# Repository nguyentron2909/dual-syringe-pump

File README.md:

# Dual Syringe Pump Controller (ESP32 + TMC2209)

This repository contains the KiCad hardware design for a compact, battery-powered dual stepper motor controller. Designed around the **ESP32-WROOM-32** for wireless control and **TMC2209** silent stepper drivers, this board is optimized for high-precision multi-channel micropump systems and drug delivery applications.

## 🛠 Hardware Architecture

The project is divided into three main functional blocks:

### 1. Power Management & Charging
A robust power subsystem designed to handle both wall power and battery operation, ensuring uninterrupted dispensing.
* **Charging:** Integrated **TP5100** battery charger for 2S Li-ion setups.
* **Regulation:** * **Buck Converter (LM2596):** Stepping down input voltage to 5V for logic.
    * **LDO (AMS1117-3.3):** Providing stable 3.3V for the ESP32 and sensors.
    * **Dual Boost Converters (XL6009):** Independent 12V rails (`+12V_1` and `+12V_2`) to power the stepper drivers, allowing for high-torque performance even on battery power.

### 2. Main Control & Interface
The logic center of the board, featuring:
* **MCU:** ESP32-WROOM-32 with USB-C programming via **CH340C** and an auto-reset circuit.
* **Position Feedback:** Support for dual **AS5600** magnetic encoders via I2C for closed-loop monitoring and exact position tracking.
* **User Interface:** Headers for an external screen, status LEDs, and additional tactile buttons.

### 3. Stepper Driver Stage
High-performance motor control featuring:
* **Drivers:** Dual **TMC2209-LA** drivers (U6 & U7).
* **Communication:** UART interface mapped to the ESP32 for advanced configuration (StealthChop, StallGuard, dynamic current limits).
* **Optimization:** Support for hardware-level current sensing. *(Note: RS resistors should be desoldered from the current sensing module for better performance, as noted in the schematic).*

---

## 📋 Key Specifications

| Component | Specification |
| :--- | :--- |
| **Microcontroller** | ESP32-WROOM-32 (Wi-Fi/BT) |
| **Stepper Drivers** | 2x TMC2209 (SilentStepStick style) |
| **Input Voltage** | +12V Adapter or 2S Li-ion Battery |
| **Logic Voltage** | 3.3V and 5V |
| **Sensors** | 2x AS5600 Magnetic Encoders |
| **USB Interface** | USB-C (CH340C) |

---

## 📂 PCB layout

---

## 📝 Design Notes

* **Current Sensing:** Ensure you desolder the RS resistors from the driver modules if you are using an external current sensing setup to avoid interference.
* **Thermal Management:** Provide adequate cooling (heatsinks/airflow) for the XL6009 boost converters and TMC2209 drivers if running the stepper motors at high continuous currents.
* **Big thanks to google gemini for writting this for me :D

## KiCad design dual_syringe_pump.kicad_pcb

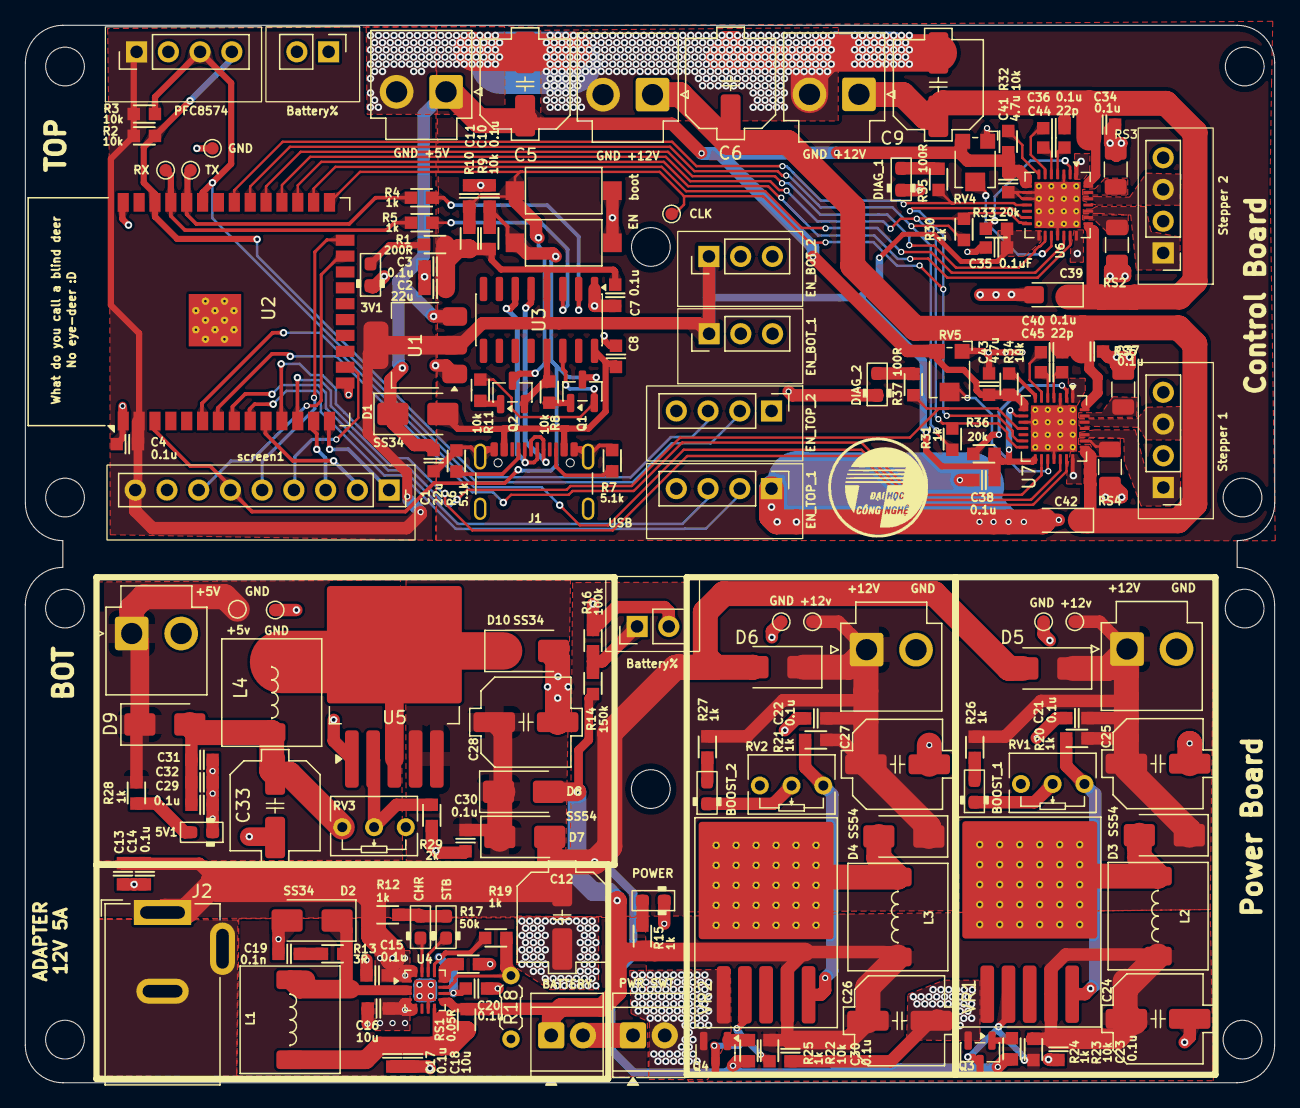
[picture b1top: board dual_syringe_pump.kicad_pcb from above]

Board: 2 copper layers, 100.0 x 84.6 mm, 161 parts (0 on the bottom side), 97 nets.

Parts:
3V1, 5V1: LED; LED_0603_1608Metric_Pad1.05x0.95mm
+5V    GND: buck; JST_VH_B2P-VH-B_1x02_P3.96mm_Vertical
+12V     GND: boost_2; JST_VH_B2P-VH-B_1x02_P3.96mm_Vertical
+12V     GND#2: boost_1; JST_VH_B2P-VH-B_1x02_P3.96mm_Vertical
BATTERY: Bat_protected; TerminalBlock_TE_282834-2_1x02_P2.54mm_Horizontal
BOOST_1, BOOST_2: LED; LED_0603_1608Metric_Pad1.05x0.95mm
Battery%: battery _percentage; PinHeader_1x02_P2.54mm_Vertical
Battery%#2: battery _percentage; PinHeader_1x02_P2.54mm_Vertical
C1, C2: 22u; C_0603
C3, C4, C7, C10, C13, C15, C17, C20, C21, C22, C23, C30, C30#2, C31, C34, C36, C37, C38, C40: 0.1u; C_0603
C5, C6, C9, C12, C25, C27, C28, C33: 100uF; C_Elec_6.3x7.7
C8, C11, C14, C29, C32, C35: 0.1uF; C_0603
C16, C18: 10u; C_0603
C19: 0.1n; C_0603
C24, C26: 330uF; C_Elec_6.3x7.7
C39, C42: 100uF; CP_EIA-3216-12_Kemet-S_HandSolder
C41, C43: 4.7u; C_0603
C44, C45: 22p; C_0603
CHR: LED; LED_0603_1608Metric_Pad1.05x0.95mm
D1, D2, D9, D10: SS34; D_SMA
D3, D4, D5, D6, D7, D8: SS54; D_SMA
DIAG_1, DIAG_2: LED; LED_0603_1608Metric_Pad1.05x0.95mm
EN_BOT_1, EN_BOT_2: Conn_01x03; PinHeader_1x03_P2.54mm_Vertical
EN_TOP_1, EN_TOP_2: Conn_01x04; PinHeader_1x04_P2.54mm_Vertical
GND: TestPoint; TestPoint_Pad_D1.0mm
GND +5V: buck; JST_VH_B2P-VH-B_1x02_P3.96mm_Vertical
GND +12V: boost_2; JST_VH_B2P-VH-B_1x02_P3.96mm_Vertical
GND +12V#2: boost_1; JST_VH_B2P-VH-B_1x02_P3.96mm_Vertical
J1: USB_C_Receptacle_USB2.0_16P; USB_C_Receptacle_GCT_USB4105-xx-A_16P_TopMnt_Horizontal
J2: Barrel_Jack_Switch_Pin3Ring; BarrelJack_GCT_DCJ200-10-A_Horizontal
L1: 22uH; L_7.3x7.3_H4.5
L2, L3: 47uH; L_7.3x7.3_H4.5
L4: 33uH; L_7.3x7.3_H4.5
PFC8574: Conn_01x04; PinHeader_1x04_P2.54mm_Vertical
POWER: LED; LED_0603_1608Metric_Pad1.05x0.95mm
PWR SWT: pb; TerminalBlock_TE_282834-2_1x02_P2.54mm_Horizontal
Q1, Q2, Q3, Q4: SS8050; SOT-23
R1: 200R; R_0603
R2, R3, R8, R9, R10, R11, R22, R23, R32, R34: 10k; R_0603
R4, R5, R12, R15, R19, R20, R21, R24, R25, R26, R27, R28, R30, R31: 1k; R_0603
R6, R7: 5.1k; R_0603
R13: 3R; R_0603
R14: 150k; R_0603
R16: 100k; R_0603
R17: 50k; R_0603
R18: 47d 3950 (10K); R_Axial_DIN0204_L3.6mm_D1.6mm_P5.08mm_Horizontal
R29: 2k; R_0603
R33, R36: 20k; R_0603
R35, R37: 100R; R_0603
RS1: 0.05R; R_0603
RS2, RS3, RS4, RS5: 0.1R; R_1206_3216Metric
RV1, RV2, RV3: 10k; Potentiometer_Bourns_3266Y_Vertical
RV4, RV5: 20k; Potentiometer_Bourns_TC33X_Vertical
STB: LED; LED_0603_1608Metric_Pad1.05x0.95mm
SW1: boot; SW_SPST_CK_RS282G05A3
SW2: reset; SW_SPST_CK_RS282G05A3
Stepper 1, Stepper 2: Conn_01x04; PinHeader_1x04_P2.54mm_Vertical
TP1: clock; TestPoint_Pad_D1.0mm
TP2: rx; TestPoint_Pad_D1.0mm
TP3: tx; TestPoint_Pad_D1.0mm
TP4, TP5, TP6, TP7, TP8, TP9: TestPoint; TestPoint_Pad_D1.0mm
U1: AMS1117-3.3; SOT-223-3_TabPin2
U2: ESP32-WROOM-32
U3: CH340C; SOIC-16_3.9x9.9mm_P1.27mm
U4: TP5100; LQFN-16-1EP_3x3mm_P0.5mm_EP1.7x1.7mm
U5: XL4015; TO-263-5_TabPin3
U6, U7: TMC2209-LA; VQFN-28-1EP_5x5mm_P0.5mm_EP3.7x3.7mm_ThermalVias
VR1, VR2: XL6019; TO-263-5_TabPin6_ThermalVias
screen1: Conn_01x09_Pin; PinSocket_1x09_P2.54mm_Vertical

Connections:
+3.3V: C2.1, C3.1, C4.1, C7.1, C35.2, C38.2, EN_BOT_1.1, EN_BOT_2.1, PFC8574.1, R1.2, R2.1, R3.1, R9.1, R10.1, R33.1, R36.1, U1.2 (VO), U2.2 (VDD), U3.4 (V3), U6.15 (VCC_IO), U7.9 (MS1/AD0), U7.15 (VCC_IO), screen1.9
+5V: +5V GND.1, C1.1, C5.1, C41.2, C43.2, D1.1 (K), D9.1 (K), GND +5V.1, R28.2, R32.1, R34.1, RV4.3, RV5.3, TP8.1, U1.3 (VI), U6.8 (5VOUT), U7.8 (5VOUT)
+12V_1: +12V GND#2.1, C9.1, C21.1, C25.1, C34.1, C36.1, C39.1, D3.1 (K), D5.1 (K), GND +12V#2.1, R20.2, R26.2, TP4.1, U6.22 (VS), U6.28 (VS)
+12V_2: +12V GND.1, C6.1, C22.1, C27.1, C37.1, C40.1, C42.1, D4.1 (K), D6.1 (K), GND +12V.1, R21.2, R27.2, TP5.1, U7.22 (VS), U7.28 (VS)
/BACKLIGHT: U2.10 (IO25), screen1.2
/CS: U2.23 (IO15), screen1.7
/D+: J1.A6 (D+), J1.B6 (D+), U3.5 (UD+)
/D-: J1.A7 (D-), J1.B7 (D-), U3.6 (UD-)
/DC: U2.24 (IO2), screen1.5
/DTR: Q2.2 (E), R8.1, U3.13 (~DTR)
/MISO: U2.14 (IO12), screen1.1
/MOSI: U2.16 (IO13), screen1.4
/Power Circuits/FB: R29.2, RV3.2, U5.2 (FB)
/Power Circuits/NTC: R18.2 (-), R19.2, U4.11 (TS)
/Power Circuits/Vreg: C20.1, R19.1, U4.10 (VREG), U4.13 (CS)
/RST: Q1.2 (E), R11.2, U3.14 (~RTS)
/RX: R5.2, TP2.1, U2.35 (TXD0/IO1)
/SCK: U2.13 (IO14), screen1.3
/SCL: EN_TOP_2.3, PFC8574.4, R2.2, U2.36 (IO22)
/SCL1: EN_TOP_1.3, U2.8 (IO32)
/SDA: EN_TOP_2.2, PFC8574.3, R3.2, U2.33 (IO21)
/SDA1: EN_TOP_1.2, U2.9 (IO33)
/TX: R4.2, TP3.1, U2.34 (RXD0/IO3)
/esp_EN: C10.1, Q1.3 (C), R9.2, SW1.1, U2.3 (EN), screen1.6
Adapter_+12V: C12.1, C13.1, C14.1, C15.1, C16.1, D5.2 (A), D6.2 (A), D7.2 (A), J2.1, R12.1, R24.2, R25.2, U4.1 (VIN), U4.4 (VIN), U4.5 (VIN), U4.16 (VIN)
DIAG_1: R35.2, U2.31 (IO19), U6.11 (DIAG)
DIAG_2: R37.2, U2.12 (IO27), U7.11 (DIAG)
DIR_1: U2.26 (IO4), U6.19 (DIR)
DIR_2: U2.6 (IO34), U7.19 (DIR)
EN_1: U2.27 (IO16), U6.20 (STDBY)
EN_2: U2.11 (IO26), U7.20 (STDBY)
Earth: BATTERY.2 (-), C12.2, C13.2, C14.2, C15.2, C16.2, C17.2, C18.2, C19.2, C20.2, D2.2 (A), J2.2, J2.3, PWR SWT.1, R17.1, R18.1 (+), U4.7 (GND), U4.17 (EXP)
GND: 5V1.1 (K), +5V GND.2, +12V GND.2, +12V GND#2.2, BOOST_1.1 (K), BOOST_2.1 (K), Battery%.2, C21.2, C22.2, C23.2, C24.2, C25.2, C26.2, C27.2, C28.2, C29.2, C30.2, C30#2.2, C31.2, C32.2, C33.2, D10.2 (A), POWER.1 (K), PWR SWT.2, Q3.2 (E), Q4.2 (E), R16.2, R29.1, RV1.2, RV2.2, TP6.1, TP7.1, TP9.1, U5.1 (GND), VR1.1 (GND), VR2.1 (GND)
GND1: 3V1.1 (K), C1.2, C2.2, C3.2, C4.2, C5.2, C6.2, C7.2, C8.2, C9.2, C10.2, C11.2, C34.2, C35.1, C37.2, C38.1, C39.2, C41.1, C42.2, C43.1, DIAG_1.1 (K), DIAG_2.1 (K), EN_BOT_1.3, EN_BOT_2.3, EN_TOP_1.1, EN_TOP_2.1, GND.1, GND +5V.2, GND +12V.2, GND +12V#2.2, J1.A1 (GND), J1.A12 (GND), J1.B1 (GND), J1.B12 (GND), J1.S1 (SHIELD), PFC8574.2, R6.1, R7.2, RS2.2, RS3.2, RS4.2, RS5.2, RV4.1, RV5.1, SW1.2, SW2.2, U1.1 (GND), U2.1 (GND), U2.15 (GND), U2.38 (GND), U2.39 (GND), U3.1 (GND), U6.3 (GND), U6.9 (MS1/AD0), U6.10 (MS2/AD1), U6.18 (GND), U6.29 (GND), U7.3 (GND), U7.10 (MS2/AD1), U7.18 (GND), U7.29 (GND), screen1.8
unnamed: 3V1.2 (A), R1.1
unnamed: 5V1.2 (A), R28.1
unnamed: BOOST_1.2 (A), R26.1
unnamed: BOOST_2.2 (A), R27.1
unnamed: C19.1, R13.1
unnamed: CHR.2 (A), R12.2, STB.2 (A)
unnamed: CHR.1 (K), U4.15 (~CHRG)
unnamed: D2.1 (K), L1.1, R13.2, U4.2 (LX), U4.3 (LX)
unnamed: D3.2 (A), L2.2, VR1.3 (SW), VR1.6 (SW)
unnamed: D4.2 (A), L3.2, VR2.3 (SW), VR2.6 (SW)
unnamed: C28.1, C30.1, D7.1 (K), D8.1 (K), U5.4 (VC), U5.5 (VIN)
unnamed: C29.1, C31.1, C32.1, C33.1, D9.2 (A), L4.2, RV3.1
unnamed: D10.1 (K), L4.1, U5.3 (SW)
unnamed: DIAG_1.2 (A), R35.1
unnamed: DIAG_2.2 (A), R37.1
unnamed: J1.A5 (CC1), R6.2
unnamed: J1.B5 (CC2), R7.1
unnamed: Q1.1 (B), R8.2
unnamed: Q2.1 (B), R11.1
unnamed: Q3.1 (B), R24.1
unnamed: Q3.3 (C), R23.2, VR1.2 (EN)
unnamed: Q4.1 (B), R25.1
unnamed: Q4.3 (C), R22.2, VR2.2 (EN)
unnamed: STB.1 (K), U4.14 (~STDBY)
unnamed: Stepper 2.1, U6.24 (OA1)
unnamed: Stepper 2.2, U6.21 (OA2)
unnamed: Stepper 2.3, U6.26 (OB1)
unnamed: Stepper 2.4, U6.1 (OB2)
unnamed: Stepper 1.1, U7.24 (OA1)
unnamed: Stepper 1.2, U7.21 (OA2)
unnamed: Stepper 1.3, U7.26 (OB1)
unnamed: Stepper 1.4, U7.1 (OB2)
unnamed: R5.1, U3.3 (RXD)
unnamed: R4.1, U3.2 (TXD)
unnamed: R17.2, U4.12 (RTRICK)
unnamed: C17.1, C18.1, L1.2, RS1.2, U4.8 (VS)
unnamed: RS2.1, U6.23 (BRA)
unnamed: RS3.1, U6.27 (BRB)
unnamed: C44.2, U6.5 (CPI)
unnamed: C44.1, U6.4 (CPO)
unnamed: R32.2, U6.7 (SPREAD)
unnamed: C36.2, U6.6 (VCP)
unnamed: RV4.2, U6.17 (VREF)
unnamed: R33.2, U6.2 (~EN)
unnamed: RS4.1, U7.23 (BRA)
unnamed: RS5.1, U7.27 (BRB)
unnamed: C45.2, U7.5 (CPI)
unnamed: C45.1, U7.4 (CPO)
unnamed: R34.2, U7.7 (SPREAD)
unnamed: C40.2, U7.6 (VCP)
unnamed: RV5.2, U7.17 (VREF)
unnamed: R36.2, U7.2 (~EN)
unnamed: R20.1, RV1.3, VR1.5 (FB)
unnamed: R21.1, RV2.3, VR2.5 (FB)
unnamed: POWER.2 (A), R15.1
unnamed: Battery%.1, R14.2, R16.1
RX_TMC: R30.2, R31.2, U2.28 (IO17), U6.14 (~PD/UART), U7.14 (~PD/UART)
STEP_1: U2.29 (IO5), U6.16 (STEP)
STEP_2: U2.7 (IO35), U7.16 (STEP)
TX_TMC: R30.1, R31.1, U2.30 (IO18)
USB_5V: C8.1, D1.2 (A), J1.A4 (VBUS), J1.A9 (VBUS), J1.B4 (VBUS), J1.B9 (VBUS), U3.16 (VCC)
Vbat: BATTERY.1 (+), C23.1, C24.1, C26.1, C30#2.1, D8.2 (A), L2.1, L3.1, R14.1, R15.2, R22.1, R23.1, RS1.1, U4.9 (BAT), VR1.4 (VIN), VR2.4 (VIN)
esp32_CLK: C11.1, Q2.3 (C), R10.2, SW2.1, TP1.1, U2.25 (IO0), U6.13 (CLK), U7.13 (CLK)

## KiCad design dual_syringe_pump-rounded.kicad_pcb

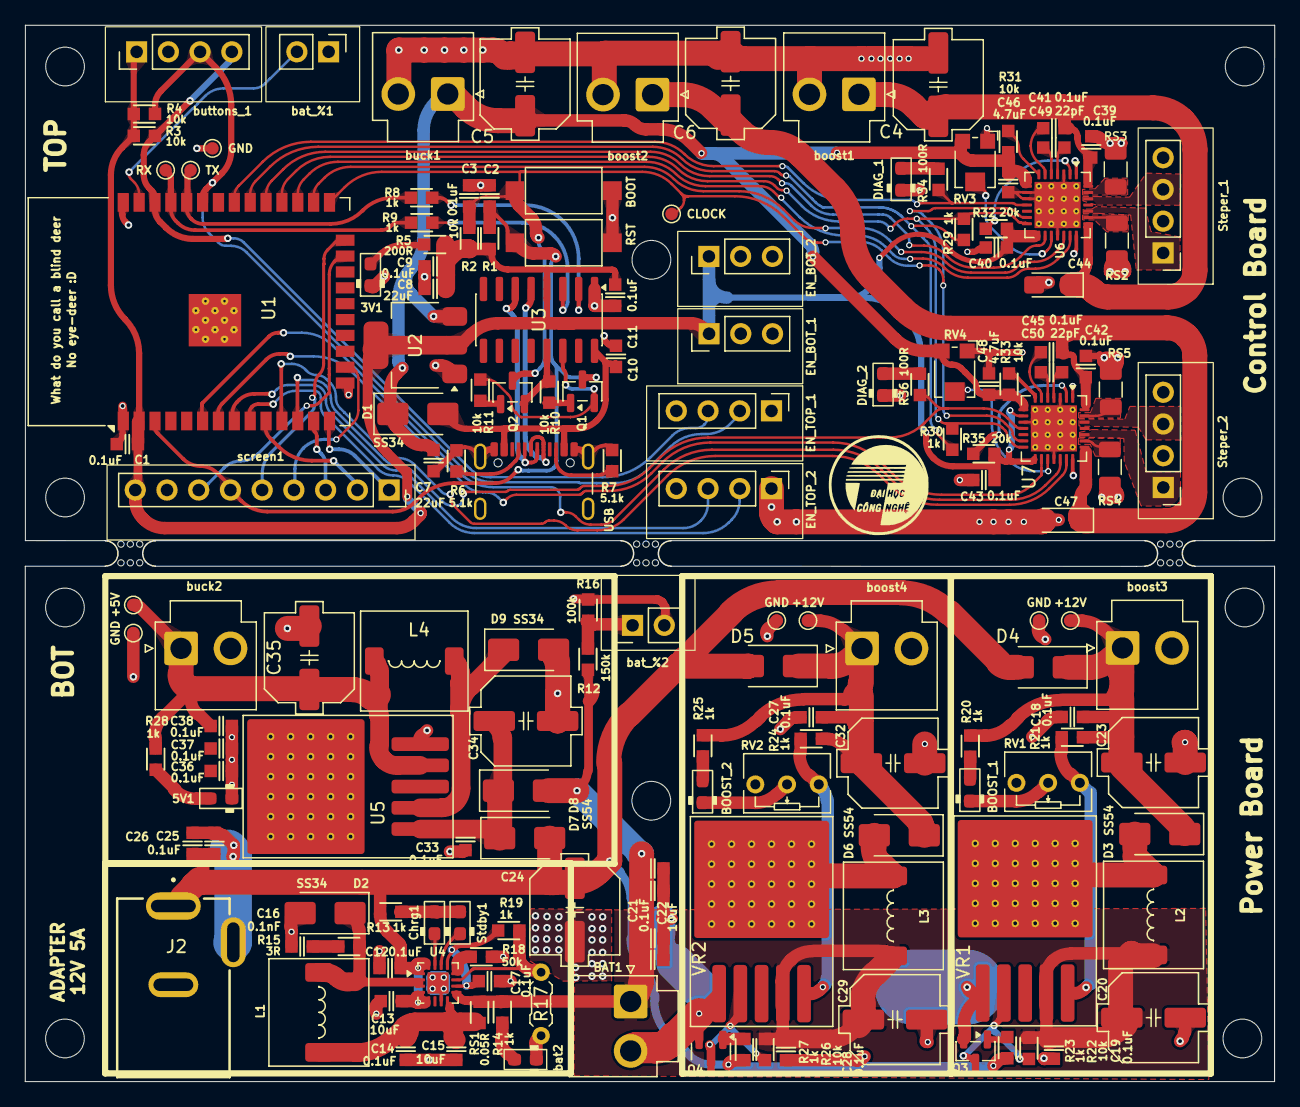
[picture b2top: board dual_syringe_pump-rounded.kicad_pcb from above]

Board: 2 copper layers, 100.0 x 84.6 mm, 164 parts (0 on the bottom side), 95 nets.

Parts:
3V1, 5V1: LED; LED_0603_1608Metric_Pad1.05x0.95mm
+5V, +12V, +12V#2: TestPoint; TestPoint_Pad_D1.0mm
BAT1: Bat_protected; JST_VH_B2P-VH-B_1x02_P3.96mm_Vertical
BOOST_1, BOOST_2: LED; LED_0603_1608Metric_Pad1.05x0.95mm
BOOT: reset; SW_SPST_CK_RS282G05A3
C1, C2, C3, C9, C10, C11, C12, C14, C17, C18, C19, C21, C25, C26, C27, C28, C30, C33, C36, C37, C38, C39, C40, C41, C42, C43, C45: 0.1uF; C_0603
C4, C5, C6, C23, C24, C32, C34, C35: 100uF; C_Elec_6.3x7.7
C7, C8: 22uF; C_0603
C13, C15, C22, C31: 10uF; C_0603
C16: 0.1nF; C_0603
C20, C29: 330uF; C_Elec_6.3x7.7
C44, C47: 100uF; CP_EIA-3216-12_Kemet-S_HandSolder
C46, C48: 4.7uF; C_0603
C49, C50: 22pF; C_0603
CLOCK: TestPoint; TestPoint_Pad_D1.0mm
Chrg1: LED; LED_0603_1608Metric_Pad1.05x0.95mm
D1, D2, D9: SS34; D_SMA
D3, D4, D5, D6, D7, D8: SS54; D_SMA
DIAG_1, DIAG_2: LED; LED_0603_1608Metric_Pad1.05x0.95mm
EN_BOT_1, EN_BOT_2: Conn_01x03; PinHeader_1x03_P2.54mm_Vertical
EN_TOP_1, EN_TOP_2: Conn_01x04; PinHeader_1x04_P2.54mm_Vertical
GND: TestPoint; TestPoint_Pad_D1.0mm
GND#2, GND#3, GND#4: TestPoint; TestPoint_Pad_D1.0mm
J2: Barrel_Jack_Switch_Pin3Ring; GCT_DCJ200-10-A-XX-K_REVA
L1: 22uH; L_7.3x7.3_H4.5
L2, L3: 47uH; L_7.3x7.3_H4.5
L4: 33uH; L_7.3x7.3_H4.5
Q1, Q2, Q3, Q4: SS8050; SOT-23
R1, R2, R3, R4, R10, R11, R22, R26, R31, R33: 10k; R_0603
R5: 200R; R_0603
R6, R7: 5.1k; R_0603
R8, R9, R13, R14, R19, R20, R21, R23, R24, R25, R27, R28, R29, R30: 1k; R_0603
R12: 150k; R_0603
R15: 3R; R_0603
R16: 100k; R_0603
R17: 47d 3950 (10K); R_Axial_DIN0204_L3.6mm_D1.6mm_P5.08mm_Horizontal
R18: 50k; R_0603
R32, R35: 20k; R_0603
R34, R36: 100R; R_0603
RS1: 0.05R; R_0603
RS2, RS3, RS4, RS5: 0.1R; R_1206_3216Metric
RST: boot; SW_SPST_CK_RS282G05A3
RV1, RV2: 10k; Potentiometer_Bourns_3266Y_Vertical
RV3, RV4: 20k; Potentiometer_Bourns_TC33X_Vertical
RX: TestPoint; TestPoint_Pad_D1.0mm
Stdby1: LED; LED_0603_1608Metric_Pad1.05x0.95mm
Steper_1, Steper_2: Conn_01x04; PinHeader_1x04_P2.54mm_Vertical
TX: TestPoint; TestPoint_Pad_D1.0mm
U1: ESP32-WROOM-32
U2: AMS1117-3.3; SOT-223-3_TabPin2
U3: CH340C; SOIC-16_3.9x9.9mm_P1.27mm
U4: TP5100; LQFN-16-1EP_3x3mm_P0.5mm_EP1.7x1.7mm
U5: LM2596S-buck; TO-263-5_TabPin3_ThermalVias
U6, U7: TMC2209-LA; VQFN-28-1EP_5x5mm_P0.5mm_EP3.7x3.7mm_ThermalVias
USB: USB_C_Receptacle_USB2.0_16P; USB_C_Receptacle_GCT_USB4105-xx-A_16P_TopMnt_Horizontal
VR1, VR2: XL6019; TO-263-5_TabPin6_ThermalVias
bat2: LED; LED_0603_1608Metric_Pad1.05x0.95mm
bat_%1, bat_%2: battery _percentage; PinHeader_1x02_P2.54mm_Vertical
boost1, boost3: boost_1; JST_VH_B2P-VH-B_1x02_P3.96mm_Vertical
boost2, boost4: boost_2; JST_VH_B2P-VH-B_1x02_P3.96mm_Vertical
buck1, buck2: buck; JST_VH_B2P-VH-B_1x02_P3.96mm_Vertical
buttons_1: Conn_01x04; PinHeader_1x04_P2.54mm_Vertical
mouse-bite-2mm-slot, mouse-bite-2mm-slot#2, mouse-bite-2mm-slot#3: VAL**; mouse-bite-2mm-slot
screen1: Conn_01x09_Pin; PinSocket_1x09_P2.54mm_Vertical

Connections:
+3.3V: C1.1, C8.1, C9.1, C11.1, C40.2, C43.2, EN_BOT_1.1, EN_BOT_2.1, R1.1, R2.1, R3.1, R4.1, R5.2, R32.1, R35.1, U1.2 (VDD), U2.2 (VO), U3.4 (V3), U6.15 (VCC_IO), U7.9 (MS1/AD0), U7.15 (VCC_IO), buttons_1.1, screen1.9
+5V: +5V.1, C5.1, C7.1, C35.1, C36.1, C37.1, C38.1, C46.2, C48.2, D1.1 (K), L4.2, R28.2, R31.1, R33.1, RV3.3, RV4.3, U2.3 (VI), U5.4 (FB), U6.8 (5VOUT), U7.8 (5VOUT), buck1.1, buck2.1
+12V_1: +12V#2.1, C4.1, C18.1, C23.1, C39.1, C41.1, C44.1, D3.1 (K), D4.1 (K), R20.2, R21.2, U6.22 (VS), U6.28 (VS), boost1.1, boost3.1
+12V_2: +12V.1, C6.1, C27.1, C32.1, C42.1, C45.1, C47.1, D5.1 (K), D6.1 (K), R24.2, R25.2, U7.22 (VS), U7.28 (VS), boost2.1, boost4.1
/BACKLIGHT: U1.10 (IO25), screen1.2
/BTN1: U1.37 (IO23), bat_%1.2
/CS: U1.23 (IO15), screen1.7
/D+: U3.5 (UD+), USB.A6 (D+), USB.B6 (D+)
/D-: U3.6 (UD-), USB.A7 (D-), USB.B7 (D-)
/DC: U1.24 (IO2), screen1.5
/DTR: Q2.2 (E), R10.1, U3.13 (~DTR)
/MISO: U1.14 (IO12), screen1.1
/MOSI: U1.16 (IO13), screen1.4
/Power Circuits/NTC: R17.2 (-), R19.2, U4.11 (TS)
/Power Circuits/Vreg: C17.1, R19.1, U4.10 (VREG), U4.13 (CS)
/RST: Q1.2 (E), R11.2, U3.14 (~RTS)
/RX: R9.2, RX.1, U1.35 (TXD0/IO1)
/SCK: U1.13 (IO14), screen1.3
/SCL: EN_TOP_1.3, R3.2, U1.36 (IO22), buttons_1.4
/SCL1: EN_TOP_2.3, U1.8 (IO32)
/SDA: EN_TOP_1.2, R4.2, U1.33 (IO21), buttons_1.3
/SDA1: EN_TOP_2.2, U1.9 (IO33)
/TX: R8.2, TX.1, U1.34 (RXD0/IO3)
/esp_EN: C2.1, Q1.3 (C), R1.2, RST.1, U1.3 (EN), screen1.6
Adapter_+12V: C12.1, C13.1, C24.1, C25.1, C26.1, D4.2 (A), D5.2 (A), D7.2 (A), J2.1, R13.1, R23.2, R27.2, U4.1 (VIN), U4.4 (VIN), U4.5 (VIN), U4.16 (VIN)
DIAG_1: R34.2, U1.31 (IO19), U6.11 (DIAG)
DIAG_2: R36.2, U1.12 (IO27), U7.11 (DIAG)
DIR_1: U1.26 (IO4), U6.19 (DIR)
DIR_2: U1.6 (IO34), U7.19 (DIR)
EN_1: U1.27 (IO16), U6.20 (STDBY)
EN_2: U1.11 (IO26), U7.20 (STDBY)
GND: 5V1.1 (K), BAT1.2 (-), BOOST_1.1 (K), BOOST_2.1 (K), C12.2, C13.2, C14.2, C15.2, C16.2, C17.2, C18.2, C19.2, C20.2, C21.2, C22.2, C23.2, C24.2, C25.2, C26.2, C27.2, C28.2, C29.2, C30.2, C31.2, C32.2, C33.2, C34.2, C35.2, C36.2, C37.2, C38.2, D2.2 (A), D9.2 (A), GND#2.1, GND#3.1, GND#4.1, J2.2, J2.3, Q3.2 (E), Q4.2 (E), R16.2, R17.1 (+), R18.1, RV1.2, RV2.2, U4.7 (GND), U4.17 (EXP), U5.3 (GND), U5.5 (~ON/OFF), VR1.1 (GND), VR2.1 (GND), bat2.1 (K), bat_%2.2, boost3.2, boost4.2, buck2.2
GND1: 3V1.1 (K), BOOT.2, C1.2, C2.2, C3.2, C4.2, C5.2, C6.2, C7.2, C8.2, C9.2, C10.2, C11.2, C39.2, C40.1, C42.2, C43.1, C44.2, C46.1, C47.2, C48.1, DIAG_1.1 (K), DIAG_2.1 (K), EN_BOT_1.3, EN_BOT_2.3, EN_TOP_1.1, EN_TOP_2.1, GND.1, R6.1, R7.2, RS2.2, RS3.2, RS4.2, RS5.2, RST.2, RV3.1, RV4.1, U1.1 (GND), U1.15 (GND), U1.38 (GND), U1.39 (GND), U2.1 (GND), U3.1 (GND), U6.3 (GND), U6.9 (MS1/AD0), U6.10 (MS2/AD1), U6.18 (GND), U6.29 (GND), U7.3 (GND), U7.10 (MS2/AD1), U7.18 (GND), U7.29 (GND), USB.A1 (GND), USB.A12 (GND), USB.B1 (GND), USB.B12 (GND), USB.S1 (SHIELD), bat_%1.1, boost1.2, boost2.2, buck1.2, buttons_1.2, screen1.8
unnamed: 3V1.2 (A), R5.1
unnamed: 5V1.2 (A), R28.1
unnamed: BOOST_1.2 (A), R20.1
unnamed: BOOST_2.2 (A), R25.1
unnamed: C16.1, R15.1
unnamed: Chrg1.2 (A), R13.2, Stdby1.2 (A)
unnamed: Chrg1.1 (K), U4.15 (~CHRG)
unnamed: D2.1 (K), L1.1, R15.2, U4.2 (LX), U4.3 (LX)
unnamed: D3.2 (A), L2.2, VR1.3 (SW), VR1.6 (SW)
unnamed: D6.2 (A), L3.2, VR2.3 (SW), VR2.6 (SW)
unnamed: C33.1, C34.1, D7.1 (K), D8.1 (K), U5.1 (VIN)
unnamed: D9.1 (K), L4.1, U5.2 (OUT)
unnamed: DIAG_1.2 (A), R34.1
unnamed: DIAG_2.2 (A), R36.1
unnamed: R6.2, USB.A5 (CC1)
unnamed: R7.1, USB.B5 (CC2)
unnamed: Q1.1 (B), R10.2
unnamed: Q2.1 (B), R11.1
unnamed: Q3.1 (B), R23.1
unnamed: Q3.3 (C), R22.1, VR1.2 (EN)
unnamed: Q4.1 (B), R27.1
unnamed: Q4.3 (C), R26.1, VR2.2 (EN)
unnamed: Stdby1.1 (K), U4.14 (~STDBY)
unnamed: Steper_1.1, U6.24 (OA1)
unnamed: Steper_1.2, U6.21 (OA2)
unnamed: Steper_1.3, U6.26 (OB1)
unnamed: Steper_1.4, U6.1 (OB2)
unnamed: Steper_2.1, U7.24 (OA1)
unnamed: Steper_2.2, U7.21 (OA2)
unnamed: Steper_2.3, U7.26 (OB1)
unnamed: Steper_2.4, U7.1 (OB2)
unnamed: R9.1, U3.3 (RXD)
unnamed: R8.1, U3.2 (TXD)
unnamed: R18.2, U4.12 (RTRICK)
unnamed: C14.1, C15.1, L1.2, RS1.2, U4.8 (VS)
unnamed: RS2.1, U6.23 (BRA)
unnamed: RS3.1, U6.27 (BRB)
unnamed: C49.2, U6.5 (CPI)
unnamed: C49.1, U6.4 (CPO)
unnamed: R31.2, U6.7 (SPREAD)
unnamed: C41.2, U6.6 (VCP)
unnamed: RV3.2, U6.17 (VREF)
unnamed: R32.2, U6.2 (~EN)
unnamed: RS4.1, U7.23 (BRA)
unnamed: RS5.1, U7.27 (BRB)
unnamed: C50.2, U7.5 (CPI)
unnamed: C50.1, U7.4 (CPO)
unnamed: R33.2, U7.7 (SPREAD)
unnamed: C45.2, U7.6 (VCP)
unnamed: RV4.2, U7.17 (VREF)
unnamed: R35.2, U7.2 (~EN)
unnamed: R21.1, RV1.3, VR1.5 (FB)
unnamed: R24.1, RV2.3, VR2.5 (FB)
unnamed: R14.1, bat2.2 (A)
unnamed: R12.2, R16.1, bat_%2.1
RX_TMC: R29.2, R30.2, U1.28 (IO17), U6.14 (~PD/UART), U7.14 (~PD/UART)
STEP_1: U1.29 (IO5), U6.16 (STEP)
STEP_2: U1.7 (IO35), U7.16 (STEP)
TX_TMC: R29.1, R30.1, U1.30 (IO18)
USB_5V: C10.1, D1.2 (A), U3.16 (VCC), USB.A4 (VBUS), USB.A9 (VBUS), USB.B4 (VBUS), USB.B9 (VBUS)
Vbat: BAT1.1 (+), C19.1, C20.1, C21.1, C22.1, C28.1, C29.1, C30.1, C31.1, D8.2 (A), L2.1, L3.1, R12.1, R14.2, R22.2, R26.2, RS1.1, U4.9 (BAT), VR1.4 (VIN), VR2.4 (VIN)
esp32_CLK: BOOT.1, C3.1, CLOCK.1, Q2.3 (C), R2.2, U1.25 (IO0), U6.13 (CLK), U7.13 (CLK)

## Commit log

2026-02-22 Update - 22-Feb-26
2026-02-22 added mousebite to rounded PCB
2026-02-22 made into blocks
2026-02-22 Add README for Dual Syringe Pump Controller project
    Added detailed documentation for the Dual Syringe Pump Controller project, including hardware architecture, specifications, project structure, and design notes.
2026-02-22 Add acknowledgment to Google Gemini in README
    Added acknowledgment to Google Gemini for assistance.
2026-02-22 Fix image path for PCB layout in README
    typo ffs
2026-02-23 added power button
2026-02-24 changed star gnd
2026-03-05 changed silk screen, added grid for star ground
